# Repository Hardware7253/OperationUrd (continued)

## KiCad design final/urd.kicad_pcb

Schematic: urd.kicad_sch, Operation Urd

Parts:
BT1: Battery; BAT-HLD-005-THM
C1: 68u; EEE-FN1E680P
C2, C15, C16: 1u; C_0402_1005Metric
C3: 100p/250v; C_0805_2012Metric
C4: 4.7u/250v; CP_Radial_D8.0mm_P3.50mm
C5: 100n/250v; C_1206_3216Metric
C6, C7, C10, C11, C12, C13, C19: 100n; C_0402_1005Metric
C8: 1n; C_0402_1005Metric
C9: 10u; C_0603_1608Metric
C14: 10n; C_0402_1005Metric
C17, C18: 22u; C_0805_2012Metric
C20, C21: 14p; C_0402_1005Metric
D1: ES2F-E3/5BT; D_SMB
D2: RED; LED_0603_1608Metric
FB1: 120R; L_0603_1608Metric
H1, H2, H3, H4, H5, H6, H7, H8: MountingHole; MountingHole_3.2mm_M3
J1, J5: Conn_01x05_Pin; PinHeader_1x05_P2.54mm_Vertical
J2: USB_C_Receptacle; USB_C_Receptacle_HRO_TYPE-C-31-M-12
J3: Conn_01x04_Pin; PinHeader_1x04_P2.54mm_Vertical
J4, J6: Conn_01x10_Pin; IDC-Header_2x05_P2.54mm_Vertical
JP1, JP2: SolderJumper_2_Open; PinHeader_1x02_P2.54mm_Vertical
L1: 100uH; SMDRS1275-101N
M1, M2, M3, M4, M5, M6, M7, M8, M9, M10, M11, M12, M13, M14, M15, M16, M17, M18: mouse-bite-5mm-slot
N1, N2, N3, N4, N5, N6, N7, N8: IN12
Q1: IRF644PBF; TO-220-3_Vertical
Q2, Q3, Q4, Q5, Q6, Q7, Q8, Q9: MMBTA92; SOT-23
Q10, Q11, Q12, Q13, Q14, Q15, Q16, Q17, Q18, Q19, Q20: MMBTA42; SOT-23
R1, R2, R3, R5, R8, R9, R14, R15, R16, R25, R26, R27, R28, R29, R30, R31, R32, R41, R42, R43, R44, R45, R46, R47, R48, R49, R50, R51, R52: 10k; R_0402_1005Metric
R4: 1M5; R_2512_6332Metric
R6, R7, R12, R13: 1k5; R_0402_1005Metric
R10, R11: 5k1; R_0402_1005Metric
R17, R18, R19, R20, R21, R22, R23, R24: 100k; R_0402_1005Metric
R33, R34, R35, R36, R37, R38, R39, R40: 10k; R_1206_3216Metric
R53: 100k; R_1206_3216Metric
RS1: 0.05R; R_1206_3216Metric_Pad1.30x1.75mm_HandSolder
RV1: 10k; Potentiometer_Bourns_3266W_Vertical
SW1, SW2, SW3: SW_SPST; SW_Cherry_MX_1.00u_PCB
SW4, SW5, SW6: SW_SPST; PinHeader_1x02_P2.54mm_Vertical
U1: MAX1771ESA+T; SO-8_3.9x4.9mm_P1.27mm
U2: AMS1117-3.3; SOT-223-3_TabPin2
U3: DS3231MZ; SOP-8_4.93mmxP1.27mm
U4: USBLC6-2SC6; SOT-23-6
U5: STM32F103CBTx; LQFP-48_7x7mm_P0.5mm
U6, U7, U8: 74HC595; SOIC-16_3.9x9.9mm_P1.27mm
Y1: 8Mhz; Crystal_SMD_3225-4Pin_3.2x2.5mm

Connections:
170V_1: C3.2, C4.1, C5.1, D1.1 (K), J4.10, R4.2
170V_2: J6.9, Q2.2 (E), Q3.2 (E), Q4.2 (E), Q5.2 (E), Q6.2 (E), Q7.2 (E), Q8.2 (E), Q9.2 (E), R17.2, R18.2, R19.2, R20.2, R21.2, R22.2, R23.2, R24.2
+3.3VA: C14.1, C15.1, FB1.1, U5.9 (VDDA)
+3V3_1: C7.1, C9.1, C10.1, C11.1, C12.1, C13.1, C16.1, C18.1, FB1.2, J3.4, J4.9, J5.5, JP1.1 (A), JP2.1 (A), R7.2, R12.2, R13.2, SW4.1 (A), SW5.1 (A), SW6.1 (A), U2.2 (VO), U3.4 (~RST), U3.6 (VBAT), U5.1 (VBAT), U5.24 (VDD), U5.36 (VDD), U5.48 (VDD)
+3V3_2: J6.10, R44.2, U6.10 (~SRCLR), U6.16 (VCC), U7.10 (~SRCLR), U7.16 (VCC), U8.10 (~SRCLR), U8.16 (VCC)
+3V3_3: J1.5, SW1.1 (A), SW2.1 (A), SW3.1 (A)
+BATT: BT1.1 (+), C8.1, U3.2 (VCC)
/BOOT0: R8.1, U5.44 (BOOT0)
/CONN_D+: J2.A6 (D+), J2.B6 (D+), U4.3 (I/O2)
/CONN_D-: J2.A7 (D-), J2.B7 (D-), U4.1 (I/O1)
/CURRENT_SENSE: Q1.3 (S), RS1.1, U1.8 (CS)
/DP_R: Q20.2 (E), R53.1
/DRAIN: D1.2 (A), L1.2, Q1.2 (D)
/FB_PD: R5.1, RV1.2, RV1.3
/GATE_DRIVE: Q1.1 (G), U1.1 (EXT)
/JMP_BOOT0: JP2.2 (B), R8.2, R9.2
/N0_BASE: Q2.1 (B), R17.1, R25.1
/N0_CATHODE: N1.1 (Anode), R33.1
/N0_COLLECTOR: Q2.3 (C), R33.2
/N1_BASE: Q3.1 (B), R18.1, R26.1
/N1_CATHODE: N2.1 (Anode), R34.1
/N1_COLLECTOR: Q3.3 (C), R34.2
/N2_BASE: Q4.1 (B), R19.1, R27.1
/N2_CATHODE: N3.1 (Anode), R35.1
/N2_COLLECTOR: Q4.3 (C), R35.2
/N3_BASE: Q5.1 (B), R20.1, R28.1
/N3_CATHODE: N4.1 (Anode), R36.1
/N3_COLLECTOR: Q5.3 (C), R36.2
/N4_BASE: Q6.1 (B), R21.1, R29.1
/N4_CATHODE: N5.1 (Anode), R37.1
/N4_COLLECTOR: Q6.3 (C), R37.2
/N5_BASE: Q7.1 (B), R22.1, R30.1
/N5_CATHODE: N6.1 (Anode), R38.1
/N5_COLLECTOR: Q7.3 (C), R38.2
/N6_BASE: Q8.1 (B), R23.1, R31.1
/N6_CATHODE: N7.1 (Anode), R39.1
/N6_COLLECTOR: Q8.3 (C), R39.2
/N7_BASE: Q9.1 (B), R24.1, R32.1
/N7_CATHODE: N8.1 (Anode), R40.1
/N7_COLLECTOR: Q9.3 (C), R40.2
/NRST: C19.1, U5.7 (NRST)
/PWR_LED_A: D2.2 (A), JP1.2 (B)
/PWR_LED_K: D2.1 (K), R6.1
/REF_BYPASS: C6.1, U1.5 (REF)
/SWCLK: J3.2, U5.37 (PA14)
/SWDIO: J3.3, U5.34 (PA13)
/S_0_BASE: Q10.1 (B), R41.2
/S_1_BASE: Q11.1 (B), R42.2
/S_2_BASE: Q12.1 (B), R43.2
/S_3_BASE: Q13.1 (B), R45.2
/S_4_BASE: Q14.1 (B), R46.2
/S_5_BASE: Q15.1 (B), R47.2
/S_6_BASE: Q16.1 (B), R48.2
/S_7_BASE: Q17.1 (B), R49.2
/S_8_BASE: Q18.1 (B), R50.2
/S_9_BASE: Q19.1 (B), R51.2
/S_DP_BASE: Q20.1 (B), R52.2
ADJUST_SW: R16.2, SW6.2 (B), U5.40 (PB4)
DIG_SR_CHAIN: U6.9 (QH'), U7.14 (SER)
DIG_SR_CLK_D: J6.6, U6.11 (SRCLK), U7.11 (SRCLK)
DIG_SR_CLK_H: J4.3, U5.15 (PA5)
DIG_SR_DATA_D: J6.5, U6.14 (SER)
DIG_SR_DATA_H: J4.4, U5.17 (PA7)
DIG_SR_LATCH_D: J6.7, U6.12 (RCLK), U7.12 (RCLK)
DIG_SR_LATCH_H: J4.2, U5.14 (PA4)
FB: C3.1, R4.1, RV1.1, U1.3 (FB)
GND1: BT1.2 (-), C1.2, C2.2, C4.2, C5.2, C6.2, C7.2, C8.2, C9.2, C10.2, C11.2, C12.2, C13.2, C14.2, C15.2, C16.2, C17.2, C18.2, C19.2, C20.2, C21.2, J2.A1 (GND), J2.A12 (GND), J2.B1 (GND), J2.B12 (GND), J3.1, J4.1, J5.1, R5.2, R6.2, R9.1, R10.1, R11.1, R14.1, R15.1, R16.1, RS1.2, U1.4 (SHDN), U1.6 (AGND), U1.7 (GND), U2.1 (GND), U3.5 (GND), U4.2 (GND), U5.8 (VSSA), U5.23 (VSS), U5.35 (VSS), U5.47 (VSS), Y1.2, Y1.4
GND2: J6.1, Q10.2 (E), Q11.2 (E), Q12.2 (E), Q13.2 (E), Q14.2 (E), Q15.2 (E), Q16.2 (E), Q17.2 (E), Q18.2 (E), Q19.2 (E), R53.2, U6.8 (GND), U7.8 (GND), U8.8 (GND)
GND3: J1.1, R1.1, R2.1, R3.1
HOUR_SW_D: J1.4, R1.2, SW1.2 (B)
HOUR_SW_H: J5.4, U5.41 (PB5)
HSE_IN: C20.1, U5.5 (PD0), Y1.1
HSE_OUT: C21.1, U5.6 (PD1), Y1.3
MINUTE_SW_D: J1.3, R2.2, SW2.2 (B)
MINUTE_SW_H: J5.3, U5.42 (PB6)
MODE_SW: R15.2, SW5.2 (B), U5.39 (PB3)
N0_ENABLE: R25.2, U8.4 (QE)
N1_ENABLE: R26.2, U8.3 (QD)
N2_ENABLE: R27.2, U8.2 (QC)
N3_ENABLE: R28.2, U8.1 (QB)
N4_ENABLE: R29.2, U8.5 (QF)
N5_ENABLE: R30.2, U8.6 (QG)
N6_ENABLE: R31.2, U8.7 (QH)
N7_ENABLE: R32.2, U8.15 (QA)
NIXIE_0: N1.2 (0), N2.2 (0), N3.2 (0), N4.2 (0), N5.2 (0), N6.2 (0), N7.2 (0), N8.2 (0), Q10.3 (C)
NIXIE_1: N1.11 (1), N2.11 (1), N3.11 (1), N4.11 (1), N5.11 (1), N6.11 (1), N7.11 (1), N8.11 (1), Q11.3 (C)
NIXIE_2: N1.10 (2), N2.10 (2), N3.10 (2), N4.10 (2), N5.10 (2), N6.10 (2), N7.10 (2), N8.10 (2), Q12.3 (C)
NIXIE_3: N1.9 (3), N2.9 (3), N3.9 (3), N4.9 (3), N5.9 (3), N6.9 (3), N7.9 (3), N8.9 (3), Q13.3 (C)
NIXIE_4: N1.8 (4), N2.8 (4), N3.8 (4), N4.8 (4), N5.8 (4), N6.8 (4), N7.8 (4), N8.8 (4), Q14.3 (C)
NIXIE_5: N1.7 (5), N2.7 (5), N3.7 (5), N4.7 (5), N5.7 (5), N6.7 (5), N7.7 (5), N8.7 (5), Q15.3 (C)
NIXIE_6: N1.6, N2.6, N3.6, N4.6, N5.6, N6.6, N7.6, N8.6, Q16.3 (C)
NIXIE_7: N1.5 (7), N2.5 (7), N3.5 (7), N4.5 (7), N5.5 (7), N6.5 (7), N7.5 (7), N8.5 (7), Q17.3 (C)
NIXIE_8: N1.4 (8), N2.4 (8), N3.4 (8), N4.4 (8), N5.4 (8), N6.4 (8), N7.4 (8), N8.4 (8), Q18.3 (C)
NIXIE_9: N1.3 (9), N2.3 (9), N3.3 (9), N4.3 (9), N5.3 (9), N6.3 (9), N7.3 (9), N8.3 (9), Q19.3 (C)
NIXIE_DP: N1.12 (DP), N2.12 (DP), N3.12 (DP), N4.12 (DP), N5.12 (DP), N6.12 (DP), N7.12 (DP), N8.12 (DP), Q20.3 (C)
NIX_SR_CLK_D: J6.3, U8.11 (SRCLK)
NIX_SR_CLK_H: J4.7, U5.26 (PB13)
NIX_SR_DATA_D: J6.2, U8.14 (SER)
NIX_SR_DATA_H: J4.8, U5.28 (PB15)
NIX_SR_LATCH_D: J6.4, U8.12 (RCLK)
NIX_SR_LATCH_H: J4.6, U5.25 (PB12)
POWER_SW: R14.2, SW4.2 (B), U5.38 (PA15)
SCL: R12.1, U3.8 (SCL), U5.21 (PB10)
SDA: R13.1, U3.7 (SDA), U5.22 (PB11)
SECOND_SW_D: J1.2, R3.2, SW3.2 (B)
SECOND_SW_H: J5.2, U5.43 (PB7)
SIG_0: R41.1, U6.7 (QH)
SIG_1: R42.1, U7.2 (QC)
SIG_2: R43.1, U7.3 (QD)
SIG_3: R45.1, U7.4 (QE)
SIG_4: R46.1, U7.5 (QF)
SIG_5: R47.1, U7.6 (QG)
SIG_6: R48.1, U6.3 (QD)
SIG_7: R49.1, U6.4 (QE)
SIG_8: R50.1, U6.5 (QF)
SIG_9: R51.1, U6.6 (QG)
SIG_DP: R52.1, U7.1 (QB)
SR_OE_D: J6.8, R44.1, U6.13 (~OE), U7.13 (~OE), U8.13 (~OE)
SR_OE_H: J4.5, U5.19 (PB1)
USB_CC1: J2.A5 (CC1), R11.2, U5.11 (PA1)
USB_CC2: J2.B5 (CC2), R10.2, U5.12 (PA2)
USB_D+: R7.1, U4.4 (I/O2), U5.33 (PA12)
USB_D-: U4.6 (I/O1), U5.32 (PA11)
VBUS: C1.1, C2.1, C17.1, J2.A4 (VBUS), J2.A9 (VBUS), J2.B4 (VBUS), J2.B9 (VBUS), L1.1, U1.2 (V+), U2.3 (VI), U4.5 (VBUS)

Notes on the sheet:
To nixie driver board
CL=2(CL0-Cs)=2(12-5)pF=14pF
VDDA filtering
USB Application note AN4879
https://www.youtube.com/watch?v=aVUqaB0IMh4
High Voltage Power Supply
Nixie 3
MOSI
Input Bypass
These are panel mounted
Digit Transistors
Nixie 4
R = (3.3 - 0.7) / (0.003 / 10) R = 9K Use 10k, then I = 0.26mA
CC pull down from USB Type-C Specification 3.5.7
Mounting Holes
Nixie 1
MCU
SW Debug
Connector
Nixie 2
R = V / I R = 0.01 / 2 R = 0.05 Ω 0.01v is the MAX1771 current measuring voltage
To main board
Nixie 5
Vout = Vref((R2 / R1) + 1) Vref = 1.5v Vout for this circuit is 150v-225v (intended 170v)
Feedback
IN12B digit current draw is 2.5mA - 3.5mA 0.3mA for DP digit
RTC
Mouse Bites
DP needs additional current limiting. DP uses 1/10 digit current, therefore R = 10k * 10
Digit Shift Registers
External clock
Min 22uF input/output caps
To mechanical switch breakout PCB
NSS
R = (170 - 145) / 0.003 R = 8333 Ω Use 10k, then I = 2.5mA
Nixie 6
Power Flags
Nixie Tube Driver (Board 2)
I2C pullup
USB

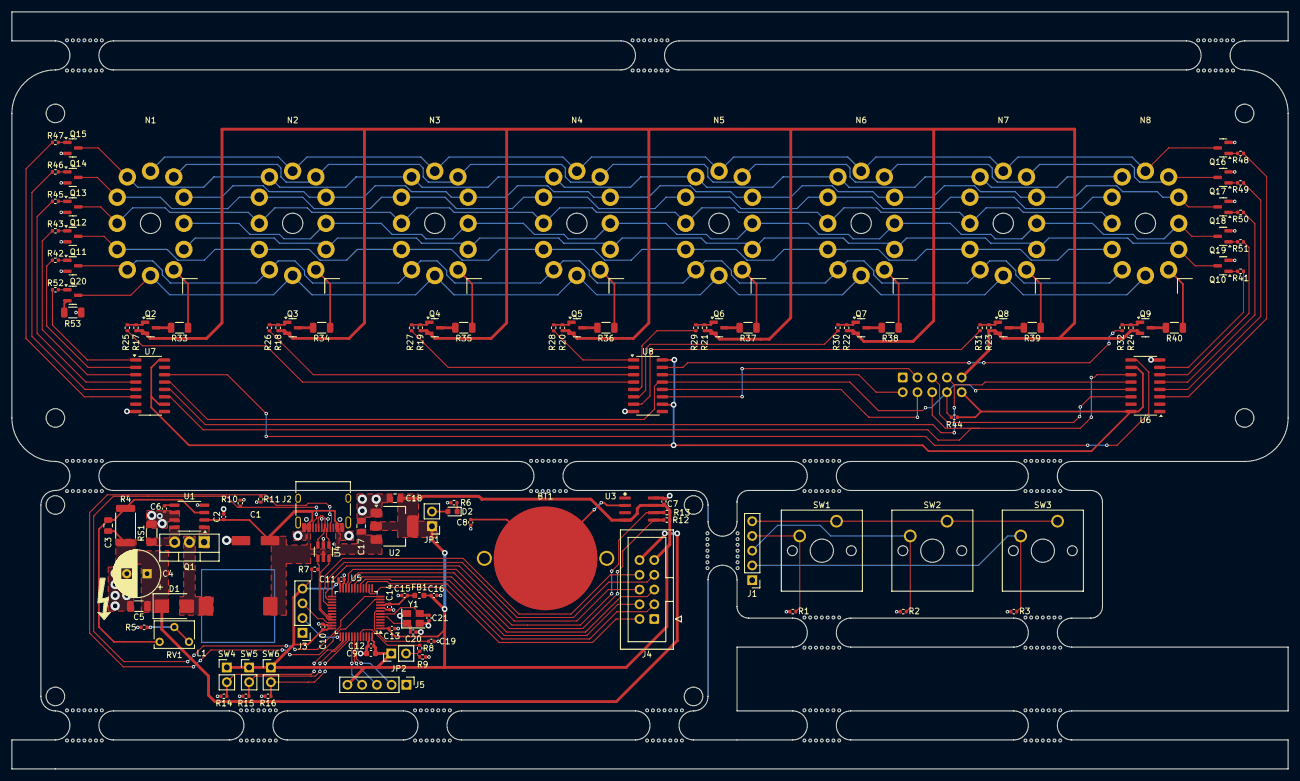
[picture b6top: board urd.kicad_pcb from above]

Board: 2 copper layers, 220.0 x 130.5 mm, 156 parts (1 on the bottom side), 124 nets.

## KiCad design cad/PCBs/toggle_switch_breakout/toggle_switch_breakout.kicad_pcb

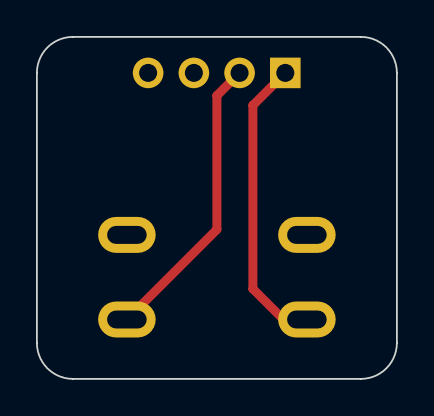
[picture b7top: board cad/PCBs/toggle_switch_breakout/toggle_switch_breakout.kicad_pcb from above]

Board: 2 copper layers, 20.0 x 19.0 mm, 3 parts (1 on the bottom side), 3 nets.

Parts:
J1: Conn_01x04_Pin; PinHeader_1x04_P2.54mm_Vertical
SW1, SW2: SW_SPST; MTS-101

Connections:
/COMMON: J1.4, SW1.1 (A), SW2.1 (A)
/SW_1: J1.2, SW1.2 (B)
/SW_2: J1.1, SW2.2 (B)

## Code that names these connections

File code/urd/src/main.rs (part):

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

    // Construct rtc using i2c bus
    let scl = gpiob.pb10.into_alternate_open_drain(&mut gpiob.crh);
    let sda = gpiob.pb11.into_alternate_open_drain(&mut gpiob.crh);

    let i2c = BlockingI2c::i2c2(
        dp.I2C2,
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
    // Construct nixies using spi bus
    let spi_pins = (
        gpiob.pb13.into_alternate_push_pull(&mut gpiob.crh), // Clock
        NoMiso, // Miso
        gpiob.pb15.into_alternate_push_pull(&mut gpiob.crh)// Mosi
    );

    let spi_mode = Mode {
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
    let mut nixies = nixies::Nixies {
        spi_bus: spi,
        latch_pin: gpiob.pb12.into_push_pull_output(&mut gpiob.crh),
        oe_pin: gpiob.pb14.into_open_drain_output(&mut gpiob.crh),
    };

    nixies.turn_off(&mut delay);
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    let mut cycle_counter = cycle_counter::Counter::new();

    // Setup switch pins has pulldown
    let on_switch_pin = gpioa.pa7.into_pull_down_input(&mut gpioa.crl);
    let mode_switch_pin = gpiob.pb0.into_pull_down_input(&mut gpiob.crl);

    // Buttons for adjusting the time
    let mut buttons = (
        button::Button::new(gpioa.pa3.into_pull_down_input(&mut gpioa.crl)), // Adjust hours
        button::Button::new(gpioa.pa4.into_pull_down_input(&mut gpioa.crl)), // Adjust minutes
        button::Button::new(gpioa.pa5.into_pull_down_input(&mut gpioa.crl)), // Adjust seconds
    );

    let mut time_adjust; // True when the users wants to adjust the clock time
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
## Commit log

2024-04-08 Added final folder
    Added folder for the final design. Completed final schematic, ready for
    trace routing.
2024-04-11 Made PCB
    Routed all traces and panelized different boards.
2024-05-29 Redesign
    Switched to a modular design, so the the entire board doesn't have to be
    re-manufactured if there is a mistake.
2024-05-29 Added script to zip gerbers
2024-06-04 Added cad directory
    Added cad directory with initial design concept drawings
2024-06-05 Changed connectors
    Changed connector from mcu to power supply to idc.
    All switches now use a straight pinheader, with no pullups (now using
    mcu pulldowns).
2024-06-06 Added ESD protection
    Added esd protection to the mcu board.
    Also added breakout board for panel mounted switches.
2024-06-08 Added casing cad files
    Designed a case in Onshape, made minor revisions to breakout boards.
2024-06-09 Added vents to case
    Added vents to the underside of the case to encourage airflow.
    Also fixed some stupid design mistakes on the PCBs. This is the night
    before EMTH btw.
2024-06-16 Changed main PCB mount
    Changed nixie board pcb mount, so now screws are visible on the front
    side of the board instead of the back. Also changed mcu i2c pullups to
    2k2.
2024-06-19 Updated cad
    Moved pcb closer to front panel so nixies protrude more.
2024-07-05 Updated cad
    Fixed heat insert hole clearances
2024-07-12 Added embedded code
    Refactored project file structure, programmed embedded firmware for
    microcontroller. Made casing wider so idc connectors have enough
    clearance to plug in. Added laser cutting drawings to cad directory.
2024-07-12 Fix .gitignore
2024-07-12 fix .gitignore for real
2024-07-12 Remove backups
2024-07-13 Changed anti-poison pattern
    Made anti-poison routine light cathodes inorder, making a wave on each
    nixie tube. Additionally, stopped the clock from ticking when in time
    adjust mode.
2024-08-17 Changed pins Changed some pins around in the embedded software to match how I assembled the project.
2024-09-10 Create LICENSE
2025-01-28 Update README.md
    Add more photos.
    Now there's a photo of it actually working
